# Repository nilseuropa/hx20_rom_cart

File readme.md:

# ROM Cartridges for the Epson HX-20

I find the HX-20 a pretty cool retro computer. Not just because it was the first ultra portable, battery operated handheld computer - in A4 format - that included a display, a printer and, a microcassette drive, but because of it's perky dual processor architecture and it's remarkable industrial design as well. It is a fairly thought through computer with a lot of accessories and endless possibilities for extensions.

I have never seen an original ROM cartridge, so I have decided to create something that would allow me to load programs quickly while on the move - the emphasis is on mobility as **Martin Hepperle's MH-20 Display and Disk Emulator** is the best thing since sliced bread when it comes to development on and for the HX-20. [Find it here](https://www.mh-aerotools.de/hp/hx-20/)

*[Original image is a courtesy of Epson](https://corporate.epson/en/about/history/milestone-products/1982-7-hx20.html)*

### Supporting documents
Fortunately Epson has a great documentation on this product:
* [Technical Manual](doc/tmH_04.pdf) - Chapter 4.2 - coverts the theory of operation and the ROM Cartridge interface.
* Technical Support Document #63a has detailed information on [ROM Format](doc/rom_fomat.md)
* Original 8/16/32k CMOS/NCMOS cartridge [schematic](doc/oschema.png)
* [Photo](doc/ROMCart.jpg) of a disassembled cartridge

#### Theory of operation
Both processors of the HX20 participate in the ROM control process. Main CPU is responsible for addressing and reading data while the register and counter are cleared by the other* CPU. *( *I know how it is called, just trying to be politically correct here. )*

First the address counter and the shift register is cleared. Then the address counter is advanced by M01, then the shift clock (MO2) provides 8 ticks to shift out a single byte serially; and that is read on MI1. That's it. The HX-20 will read the program start address from the ROM header and advance the address counter without shifting out bits until it arrives to the desired address.

## 32K ROM Cartridge
### Schematics
As modern EPROMs are not very power hungry, (J1) power select for non-c-mos type chips have been omitted along with the LDO and the utilization of SIO3 ( ROM Power on signal ). J2A is non-existent = OFF, while J2B connects rom address A14 to the last stage of binary counter output.

### 32K Board
Eagle CAD files, HX-20 cartridge port library and production gerbers are under the [hardware](/hardware) folder.

## ROM Emulator Cartridge
This emulator has an ESP32 in its heart to provide wireless ROM update capability through FTP - although I do see a potential here to use a less power hungry MCU and an SD card. Anyhow, transferring ROM files over WiFi is what I thought was cool. The firmware has been cooked as a platformio project based on the Arduino framework to make it easily portable and accessible for modifications.

:camera: [See it in action](https://photos.google.com/share/AF1QipMuma70FzuCHWNQoMt1CCRNrimfOKazqg87h7Ul6GqiaPwG6kRcX4zg7sMcNq5RkA?key=eUxmN0t5NTZiamtFMTQtWUFrUUo1dGxTRENqZnB3)

#### Interface pinout
Use 5V to 3.3V level shifters on all ESP32 inputs. The only ESP32 output, the data line can be connected directly as the interface operates with TTL levels.

| HX-20 Pin | Signal name | ESP32 Pin | Description |
| -------- | -------- | -------- | -------- |
|1|SI1|-|ROM / Cassette judgement - pulled down |
|2|SIO1|-|ROM / Cassette judgement - pulled down |
|3|SO1|-|Unused|
|4|SIO2|D22|Address counter clear|
|5|SIO3|-| Unused (ROM Power On)|
|6|SIO4|D23|Shift register clear|
|7|VB|VIN|Battery voltage
|8|MI1|D26|Data (Shift register output)|
|9|MO2|D27|Shift register clock|
|10|MO1|D25|Address counter (SHIFT/LOAD select)|
|11|G|GND|Ground|
|12|5V|-|Regulated 5V

#### Current state :warning:
This project is "under development" *( without goals or deadlines )* - there are more than a zillion ways to improve it. Also barely usable in this form, but it satisfies my use case - that is:
* I can create a ROM image on my computer with the help of Martin's `extrom` script. ( Python folder )
* Upload it to the FTP server on the cartridge. ( has to be `pac0.rom` )
* List, load and run the contents of the ROM image on the HX-20.

#### Tweak to use it :warning:

If you would like to play with it ( or make it better ) you'll need to get this repository. I highly recommend platformio ( CLI or through VSCode ) to build it. Don't forget to upload the `data` folder as well, or at least make sure you have formatted the SPIFFS, so that you can land a ROM file on it.

```uint8_t  rom_buffer[8196];``` --- ESP32 has 520K RAM so ...

```const char *ssid = "YOUR_WIFI_AP";```

```const char *password = "YOUR_WIFI_PW";```

At init it will look for `pac0.rom` and load it into `rom_buffer`. There are absolutely no checks whether that happens or not. (yet)
The contents of the filesystem are listed upon boot over serial.

#### All contributions are welcome!

* FTP server that I found is not very reliable. *( maybe assign it to a single core or dump the whole thing for something else )*
* Wifi configuration could be done through AP. ( there are libraries out there for that )
* It doesn't have to be FTP, the ESP could run a small web server with some minimal UI to make it more easier to use.
* There is a bug at initialization, the first character is always read as `1`
* The ESP is using SPIFFS on the internal 4MB flash, that can hold multiple rom files.
* ROM file selection would be great ( there are multiple good ways to do it )
  * **Web based UI** *(would make the most sense if it is used for setting wifi credentials anyway)*
  * OLED screen / buttons ( from design perspective I find it too much )
  * With some trickery *(e.g. mandatory first and last file in a ROM image would trigger rom pack switch)*
* The firmware could handle the ROM image compilation, so that raw binary and basic files could be thrown at it
* Circuit has to be designed that incorporates an LDO and MOSFET switching *( :arrow_up: SIO3 - ROM Power On )*
* I can see a variant that is based on smaller MCU with an SD card as medium. *( this is an easy port )*
* The enclosure of the cartridge needs to be modeled to make it printable

--- all right, by now.

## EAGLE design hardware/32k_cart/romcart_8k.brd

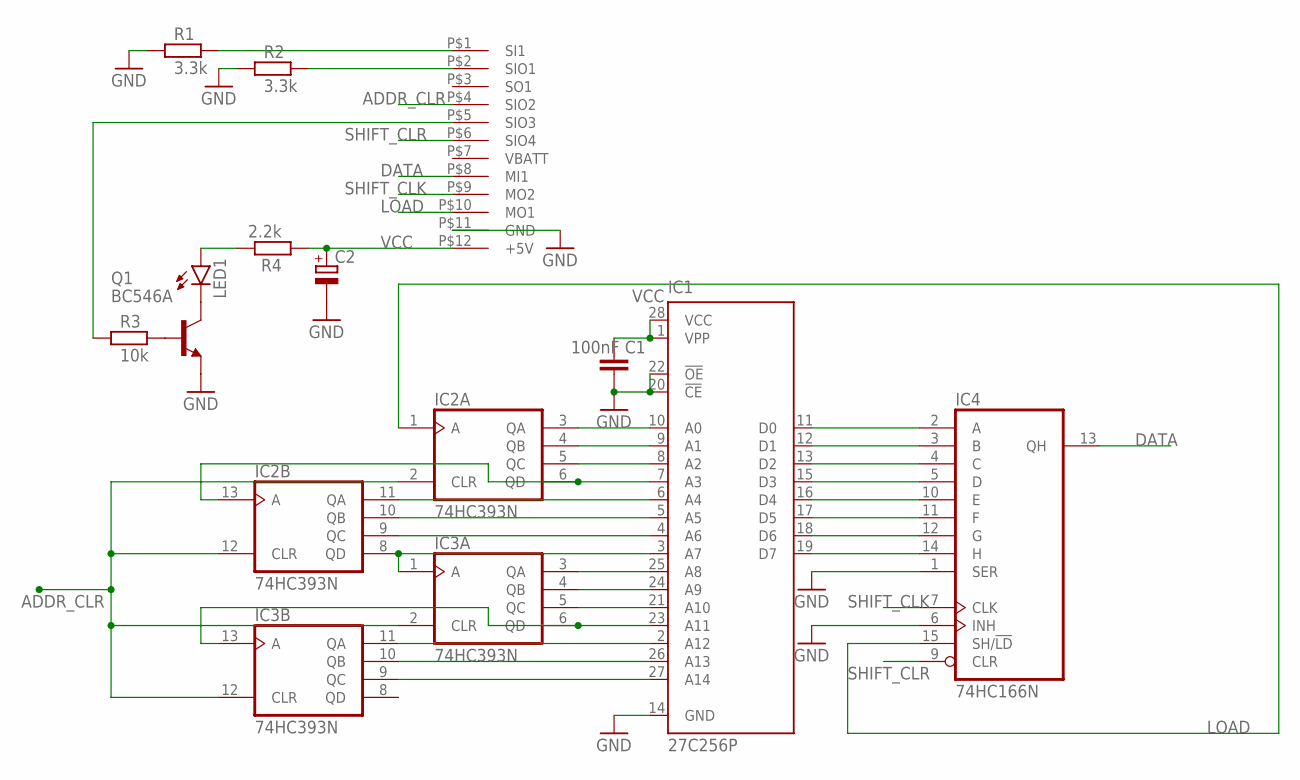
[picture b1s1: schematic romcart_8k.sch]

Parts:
C1: 100nF; C2.5-3
C2: CPOL-EUE3.5-8; E3,5-8
IC1: 27C256P; DIL28-6
IC2, IC3: 74HC393N; DIL14
IC4: 74HC166N; DIL16
LED1: LED3MM
Q1: BC546A; TO92-EBC
R1, R2: 3.3k; 0204/5
R3: 10k; 0204/5
R4: 2.2k; 0204/5
U$1: HX20_CASSETTE

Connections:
ADDR_CLR: IC2.2 (CLR), IC2.12 (CLR), IC3.2 (CLR), IC3.12 (CLR), U$1.P$4 (SIO2)
DATA: IC4.13 (QH), U$1.P$8 (MI1)
GND: C1.2, C2.-, IC1.14 (GND), IC1.20 (!CE), IC1.22 (!OE), IC2.7 (GND), IC3.7 (GND), IC4.1 (SER), IC4.6 (INH), IC4.8 (GND), Q1.E, R1.1, R2.1, U$1.P$11 (GND)
LOAD: IC2.1 (A), IC4.15 (SH/!LD), U$1.P$10 (MO1)
unnamed: IC1.10 (A0), IC2.3 (QA)
unnamed: IC1.9 (A1), IC2.4 (QB)
unnamed: IC1.8 (A2), IC2.5 (QC)
unnamed: IC1.7 (A3), IC2.6 (QD), IC2.13 (A)
unnamed: IC1.6 (A4), IC2.11 (QA)
unnamed: IC1.5 (A5), IC2.10 (QB)
unnamed: IC1.4 (A6), IC2.9 (QC)
unnamed: IC1.3 (A7), IC2.8 (QD), IC3.1 (A)
unnamed: IC1.25 (A8), IC3.3 (QA)
unnamed: IC1.24 (A9), IC3.4 (QB)
unnamed: IC1.21 (A10), IC3.5 (QC)
unnamed: IC1.23 (A11), IC3.6 (QD), IC3.13 (A)
unnamed: IC1.2 (A12), IC3.11 (QA)
unnamed: IC1.26 (A13), IC3.10 (QB)
unnamed: IC1.27 (A14), IC3.9 (QC)
unnamed: IC1.11 (D0), IC4.2 (A)
unnamed: IC1.12 (D1), IC4.3 (B)
unnamed: IC1.13 (D2), IC4.4 (C)
unnamed: IC1.15 (D3), IC4.5 (D)
unnamed: IC1.16 (D4), IC4.10 (E)
unnamed: IC1.17 (D5), IC4.11 (F)
unnamed: IC1.18 (D6), IC4.12 (G)
unnamed: IC1.19 (D7), IC4.14 (H)
unnamed: Q1.B, R3.2
unnamed: R1.2, U$1.P$1 (SI1)
unnamed: R2.2, U$1.P$2 (SIO1)
unnamed: LED1.K (C), Q1.C
unnamed: LED1.A, R4.2
unnamed: R3.1, U$1.P$5 (SIO3)
SHIFT_CLK: IC4.7 (CLK), U$1.P$9 (MO2)
SHIFT_CLR: IC4.9 (CLR), U$1.P$6 (SIO4)
VCC: C1.1, C2.+, IC1.1 (VPP), IC1.28 (VCC), IC2.14 (VCC), IC3.14 (VCC), IC4.16 (VCC), R4.1, U$1.P$12 (+5V)

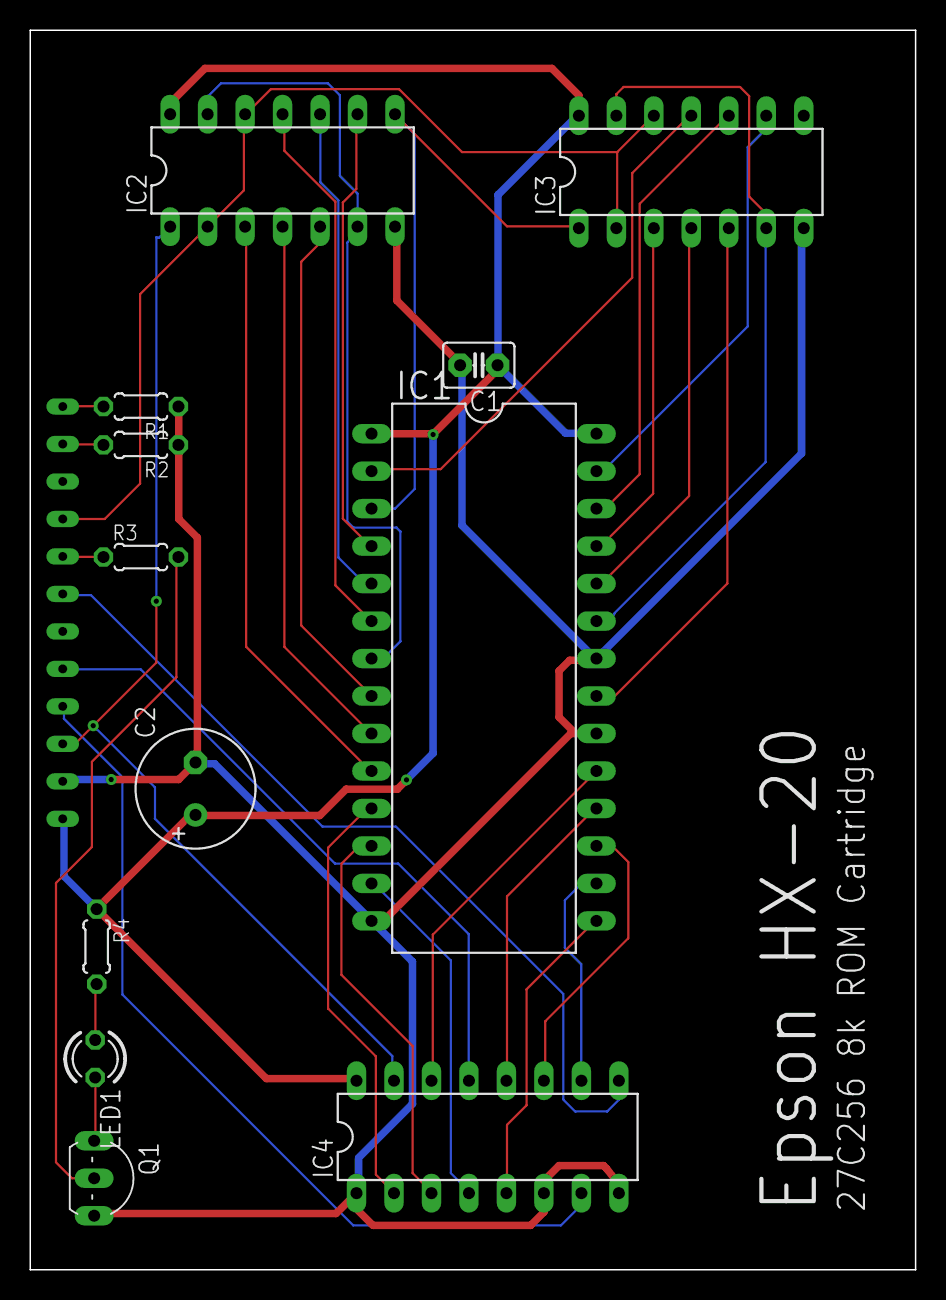
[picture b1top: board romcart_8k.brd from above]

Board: 2 copper layers, 60.0 x 84.0 mm, 13 parts (0 on the bottom side), 36 nets.

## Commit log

2024-03-14 proof of concept
2024-03-14 proof of the proof added
